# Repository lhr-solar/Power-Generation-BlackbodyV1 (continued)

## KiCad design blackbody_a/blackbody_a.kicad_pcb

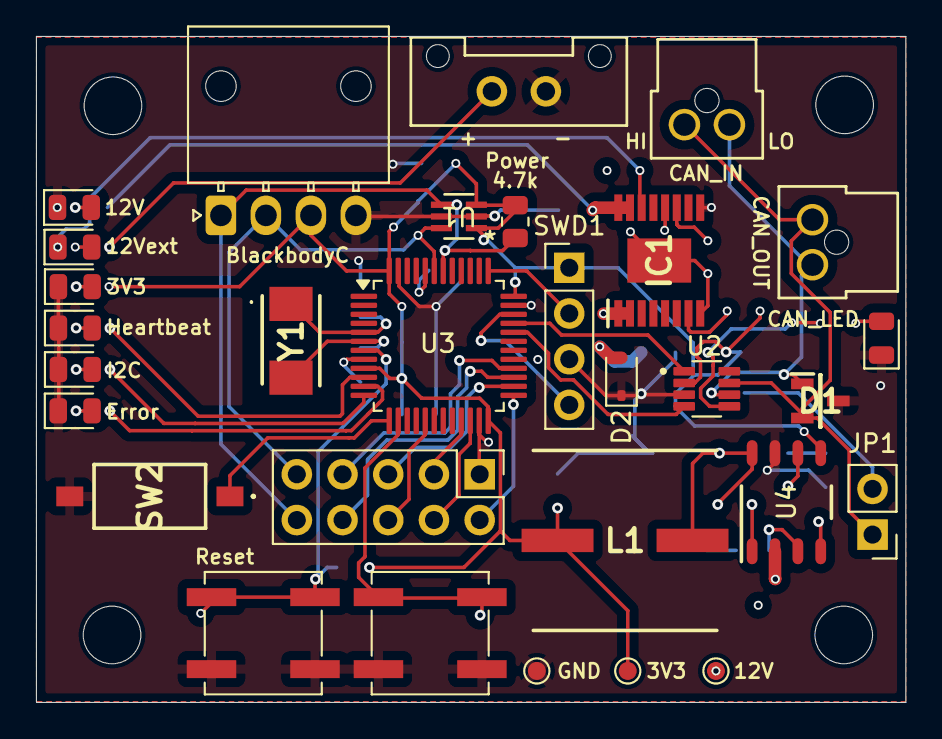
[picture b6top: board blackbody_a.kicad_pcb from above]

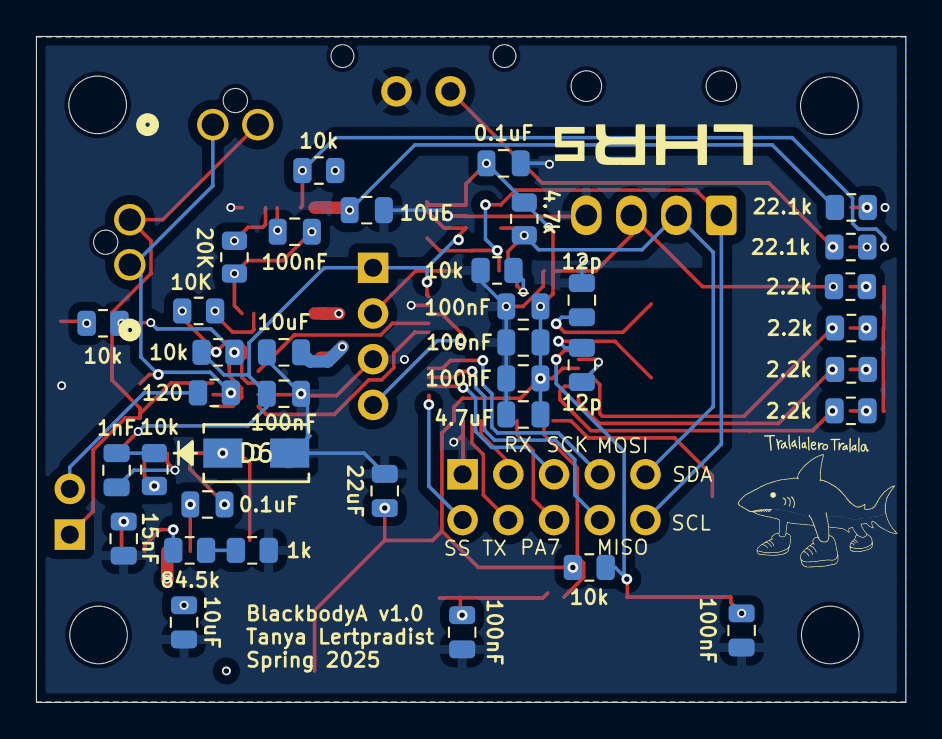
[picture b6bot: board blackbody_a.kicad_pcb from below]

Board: 4 copper layers, 48.3 x 37.0 mm, 71 parts (37 on the bottom side), 49 nets.

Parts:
3V3, 12V#2: TestPoint; TestPoint_Pad_D1.0mm
3V3#2: 3.3V; LED_0805_2012Metric
12V, 12Vext: 12V; LED_0805_2012Metric
BlackbodyC: Conn_01x04; Molex_Nano-Fit_105313-xx04_1x04_P2.50mm_Horizontal
C1, C17: 0.1uF; C_0805_2012Metric
C2, C3, C16: 10uF; C_0805_2012Metric
C4: 22uF; C_0805_2012Metric
C9, C10, C20, C21, C22, C23, C24: 100nF; C_0805_2012Metric
C12, C13: 12p; C_0805_2012Metric
C18: 15nF; C_0805_2012Metric
C19: 4.7uF; C_0805_2012Metric
C25: 1nF; C_0805_2012Metric
CAN_Err: CAN_LED; LED_0805_2012Metric
CAN_IN: Conn_01x02; CONN_SD-105309-100_02_MOL
CAN_OUT: Conn_01x02; CONN_SD-105309-100_02_MOL
D1: CDSOT23-T24CAN; SOT95P230X117-3N
D2: SD12_SOD323; D_SOD-323
D6: D; SMA_DIO
Error: Error; LED_0805_2012Metric
GND: TestPoint; TestPoint_Pad_D1.0mm
H1, H2, H3, H4: MountingHole; MountingHole_3.2mm_M3
Heartbeat: Heartbeat; LED_0805_2012Metric
I2C: I2C; LED_0805_2012Metric
IC1: LM76202QPWPRQ1
J3: Conn_02x05_Counter_Clockwise; PinHeader_2x05_P2.54mm_Vertical
JP1: Jumper_2_Open; PinHeader_1x02_P2.54mm_Vertical
L1: MSS1038-153MLC; INDPM102100X400N
Power: CarPowerConnector; Molex_MicroFit3.0_1x2xP3.00mm_PolarizingPeg_Vertical
R1, R2: 4.7k; R_0805_2012Metric
R3, R5, R9, R16, R18, R23: 10k; R_0805_2012Metric
R4: 120; R_0805_2012Metric
R8: 10K; R_0805_2012Metric
R10: 20K; R_0805_2012Metric
R13, R15: 22.1k; R_0805_2012Metric
R14, R17, R21, R22: 2.2k; R_0805_2012Metric
Reset: Reset; SW_SPST_B3SL-1002P
Rosc1: 84.5k; R_0805_2012Metric
Rosc2: 1k; R_0805_2012Metric
SW2: SW_DIP_x01; DS04254101BKSMT
SW5: SW_Push; SW_SPST_B3SL-1002P
SWD1: Conn_01x04; PinHeader_1x04_P2.54mm_Vertical
U1: LTC4311CSC6-TRPBF; SOT-6_SC_LIT
U2: TCAN337DCNR; SOT65P280X145-8N
U3: STM32L431CBTx; LQFP-48_7x7mm_P0.5mm
U4: TPS5403DR; D0008A_N
Y1: 8M; ABM3

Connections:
+3.3V: 3V3.1, BlackbodyC.3, C1.2, C4.1, C9.1, C19.1, C20.1, C21.1, C22.1, L1.2, R1.1, R2.1, R8.1, R14.1, R18.1, R23.1, SWD1.1, U1.1 (VCC), U1.3 (ENABLE), U2.2 (GND), U3.9 (VDDA), U3.24 (VDD), U3.36 (VDD), U3.48 (VDD), U4.5 (VSENSE)
+12V: 12V#2.1, C3.1, C16.2, IC1.15 (OUT_1), IC1.16 (OUT_2), R9.1, R13.1, U4.2 (VIN)
/12V_Ext: C2.1, D2.2 (A2), IC1.1 (IN_1), IC1.2 (IN_2), Power.1 (+12V), R15.1
/17: J3.6, U3.17 (PA7)
/CAN_H: CAN_IN.2, CAN_OUT.2, D1.2 (CANL), JP1.1 (A), U2.7 (CANH)
/CAN_L: CAN_IN.1, CAN_OUT.1, D1.1 (CANH), R4.1, U2.6 (CANL)
/CAN_RX: U2.4 (RXD), U3.32 (PA11)
/CAN_TX: U2.1 (TXD), U3.33 (PA12)
/Error: R17.1, U3.11 (PA1)
/Heartbeat: R22.1, U3.10 (PA0)
/I2C: R21.1, U3.12 (PA2)
/NRST: C24.2, R23.2, Reset.1, U3.7 (NRST)
/SCL: BlackbodyC.1, J3.10, R1.2, U1.4 (BUS2), U3.42 (PB6)
/SDA: BlackbodyC.2, J3.9, R2.2, U1.6 (BUS1), U3.43 (PB7)
/SPI_MISO: J3.8, U3.27 (PB14)
/SPI_MOSI: J3.7, U3.28 (PB15)
/SPI_SCK: J3.5, U3.26 (PB13)
/SPI_SS: J3.2, U3.25 (PB12)
/SWCLK: SWD1.2, U3.37 (PA14)
/SWDIO: SWD1.4, U3.34 (PA13)
/SW_PUSH: C23.1, SW5.2, U3.14 (PA4)
/SW_SLIDE: SW2.1, U3.13 (PA3)
/UART_RX: J3.3, U3.21 (PB10)
/UART_TX: J3.4, U3.22 (PB11)
/can_comm/Fault: R16.1, R18.2, U2.5 (FAULT)
/power_dist/Fault: 12Vext.1 (K), IC1.14 (~FLT), R9.2
/power_dist/RTN: C10.2, IC1.8 (RTN), IC1.17 (EP), R10.2
GND: 3V3#2.1 (K), 12V.1 (K), BlackbodyC.4, C1.1, C2.2, C3.2, C4.2, C9.2, C12.1, C13.1, C16.1, C18.2, C19.2, C20.2, C21.2, C22.2, C23.2, C24.1, C25.1, CAN_Err.1 (K), D1.3 (GND), D2.1 (A1), D6.2 (A), Error.1 (K), GND.1, Heartbeat.1 (K), I2C.1 (K), IC1.9 (GND), J3.1, Power.2 (GND), R3.2, Reset.2, Rosc2.2, SW2.2, SW5.1, SWD1.3, U1.2 (GND), U1.5 (GND), U2.3 (VCC), U3.8 (VSSA), U3.23 (VSS), U3.35 (VSS), U3.47 (VSS), U4.7 (GND)
unnamed: C25.2, R5.2
unnamed: 12V.2 (A), R13.2
unnamed: 3V3#2.2 (A), R14.2
unnamed: 12Vext.2 (A), R15.2
unnamed: C17.2, D6.1 (K), L1.1, U4.8 (LX)
unnamed: CAN_Err.2 (A), R16.2
unnamed: Error.2 (A), R17.2
unnamed: I2C.2 (A), R21.2
unnamed: Heartbeat.2 (A), R22.2
unnamed: C10.1, IC1.12 (DVDT)
unnamed: IC1.11 (ILIM), R10.1
unnamed: IC1.7 (~SHDN), R8.2
unnamed: JP1.2 (B), R4.2
unnamed: Rosc1.2, Rosc2.1
unnamed: C12.2, U3.5 (PH0), Y1.1
unnamed: C13.2, U3.6 (PH1), Y1.2
unnamed: R3.1, U3.44 (PH3)
unnamed: C17.1, U4.1 (BOOT)
unnamed: R5.1, U4.6 (COMP)
unnamed: Rosc1.1, U4.3 (ROSC)
unnamed: C18.1, U4.4 (SS)

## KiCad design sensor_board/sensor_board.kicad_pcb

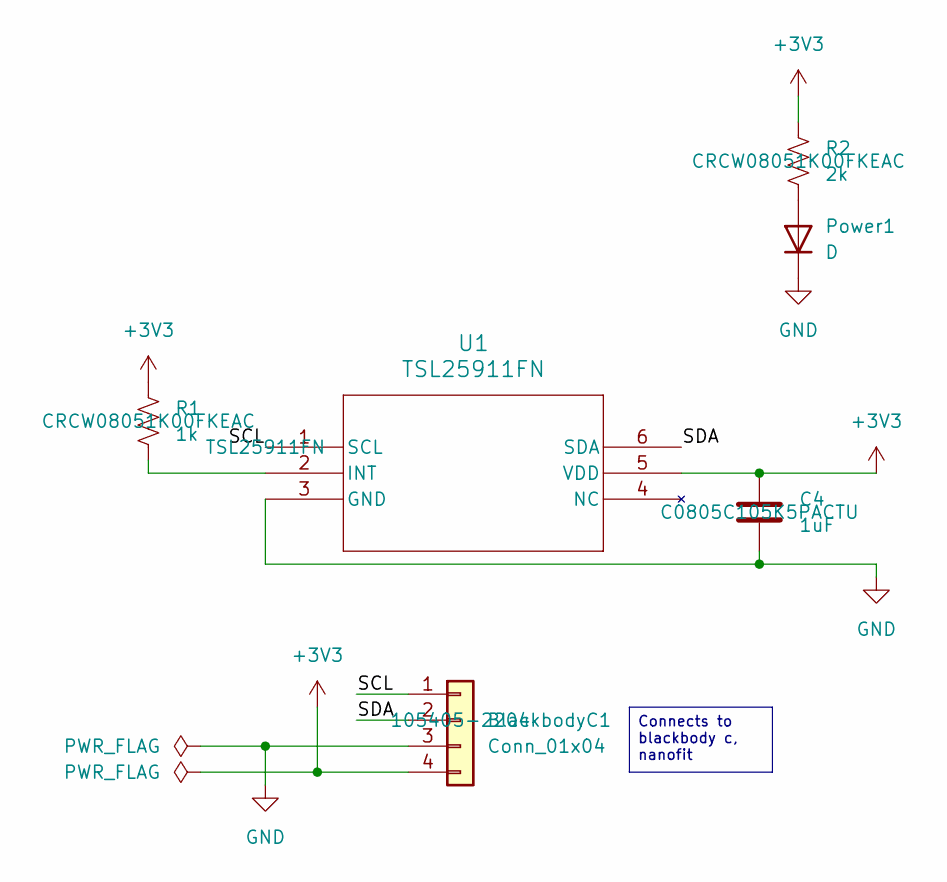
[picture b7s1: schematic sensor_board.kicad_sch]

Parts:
BlackbodyC1: Conn_01x04; CONN_SD-105429-001_04_MOL
C4: 1uF; C_0805_2012Metric
Power1: D; LED_0805_2012Metric
R1: 1k; R_0805_2012Metric
R2: 2k; R_0805_2012Metric
U1: TSL25911FN; SON-06-FN_2000X2400_AMS

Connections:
+3V3: BlackbodyC1.4, C4.2, R1.1, R2.1, U1.5 (VDD)
/SCL: BlackbodyC1.1, U1.1 (SCL)
/SDA: BlackbodyC1.2, U1.6 (SDA)
GND: BlackbodyC1.3, C4.1, Power1.1 (K), U1.3 (GND)
unnamed: Power1.2 (A), R2.2
unnamed: R1.2, U1.2 (INT)

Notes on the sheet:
Connects to blackbody c, nanofit

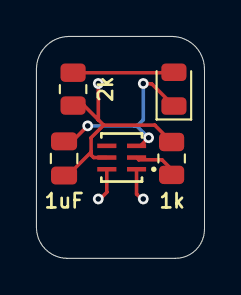
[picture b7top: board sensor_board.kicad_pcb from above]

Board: 2 copper layers, 9.3 x 12.3 mm, 6 parts (1 on the bottom side), 6 nets.

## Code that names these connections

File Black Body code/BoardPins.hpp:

#pragma once
#include "mbed.h"

// MCU: STM32G474RE

// ---- Serial 
static constexpr PinName PIN_USB_TX = _____;
static constexpr PinName PIN_USB_RX = _____;

// ---- CAN 
static constexpr PinName PIN_CAN_TX = _____;
static constexpr PinName PIN_CAN_RX = _____;

// ---- I2C1 
static constexpr PinName PIN_I2C1_SDA = _____;
static constexpr PinName PIN_I2C1_SCL = _____;

// ---- Shared interrupt line from breakout Irrad Sensor
static constexpr PinName PIN_INT = _____;

// ---- LEDs ----
static constexpr PinName PIN_LED_HEARTBEAT = _____;
static constexpr PinName PIN_LED_DB_CONN_1  = _____;
static constexpr PinName PIN_LED_DB_CONN_2  = _____;
static constexpr PinName PIN_LED_DB_CONN_3  = _____;

// ---- Feature toggles ----
static constexpr bool ENABLE_HEARTBEAT = true;
static constexpr bool ENABLE_TSL_INT   = true;

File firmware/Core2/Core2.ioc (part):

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Mcu.Name=STM32L431C(B-C)Tx
Mcu.Package=LQFP48
Mcu.UserName=STM32L431CBTx
PB6.Mode=I2C
PB6.Signal=I2C1_SCL
PB7.Mode=I2C
PB7.Signal=I2C1_SDA
RCC.HSE_VALUE=8000000
board=custom

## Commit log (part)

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2024-11-16 Git attributes
2024-11-17 sensor board
2024-12-07 added more complexity + thermistor connection
2025-01-25 Initial version of sensor communication through all three boards
2025-01-25 Updated minor errors
2025-01-31 Temperature reader update
2025-02-08 Added controller and CAN
2025-02-22 Added power distribution
2025-02-25 minor errors
2025-03-12 Fixed pins, minor changes, removed power isolation
2025-03-12 add testpoints
2025-03-12 review changes
2025-04-09 layout iteration 1
2025-04-24 layout edits
2025-05-05 layout updates
2025-05-10 fixed footprint issue
2025-09-26 Cleaned repo. Added new blackbody A kicad project
2025-10-04 Layout Added
2025-10-04 adding readme
2025-10-04 adding gitignore
2025-10-04 cleaned up files
2025-10-04 Added irradiance breakout
2025-10-04 Revision
2025-10-11 Updated Layout
2025-10-11 arc corners
2025-10-11 connector update
2025-10-11 resistors added
2025-10-15 updated bb
2025-10-18 updated silk screen
2025-10-19 updated connectors
2025-10-19 fixed edge cuts BO
2025-10-19 gebers + BOM
2025-10-19 3D models and gerber
2025-10-25 updated BOM
2025-11-01 updated 3D model
2025-11-01 moved fuse
2025-11-04 updated step file
2026-01-17 better file system
2026-01-19 swap from mx150 to nanofit
2026-01-22 Updated KiCad Sharepoint
2026-01-22 repo fix
2026-01-22 repo cleanup
2026-01-22 fixed location of kicad sharepoint
2026-01-23 new layout
2026-01-23 new layout 2.0
2026-01-23 cleaned up files for irrad board
2026-01-24 Updated layout and 3D models
2026-01-24 changed 3D models for breakout
2026-01-24 updated 3d models for aarav
2026-01-24 updated irrad board layout + removed testpoints
2026-01-24 actual irrad board update
2026-01-24 updated irrad board
2026-01-25 updated 24V
2026-01-25 updated 24Va
2026-01-28 added logic analyzer + LEDS
2026-01-28 updated fuse silkscreen, added open circuit to TC
2026-01-28 updated GND pads MCP600
2026-01-28 moved trace + cleaned up silkscreen
2026-01-29 new gerber files
2026-01-31 BOM update
2026-02-02 updated cap
2026-02-02 updated cap breakout
2026-02-02 updated resistors 0805 to 0603
2026-02-02 updated ferrite bead values
2026-02-03 updated caps
2026-02-22 irradtransmit test initalized code without recieve correct
2026-02-22 updated transmit and recieve line to be correct deleted .h files in hal_config and hal_it in embedded sharepoint still won't compile
2026-02-24 readme
2026-02-24 restructure
2026-02-24 fixed modules
2026-02-24 blinky
2026-02-26 working ack irrad test
2026-03-28 validated testing for thermo, irrad, and printf test for l4
2026-04-04 working write test for new drivers
2026-04-14 printf works
2026-04-15 full working irrad sensor + printf
2026-04-15 removed weird ahh file
2026-04-15 build.yml
2026-04-16 edited build file
2026-04-16 deleted past irrad test
2026-04-16 some shi aarav did
2026-04-16 changed gitmodules file
2026-04-16 made makeAllTests file
2026-06-23 non working push idk
2026-06-29 nonworking thermo interrupt based
